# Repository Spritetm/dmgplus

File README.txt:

These are various files for the DMGPlus project. Note that I did this over the time span
of about three years, so there's no plug-and-play recipe to build your own available;
I'd need to reverse my own work to provide that. As such, these files are only provided
as a reference, to plunder if you want to build something similar. For more information
about the DMGPlus project, refer to https://spritesmods.com/?art=dmgplus

The various subdirectories:

* kicad-pcb
This contains the PCB layout. Look at dmgplus-schematic.pdf in that directory if you only want
to look at the schematic without opening Kicad.

* fpga
This contains the Verilog sources for the Ice40 FPGA configuration. You need a proper 
Yosys/nextpnr/icestorm setup to build this.

* linux
This contains the gpio-matrix patch I had to apply to get multiple buttonpresses to work, as
well as the config I use to get the kernel startup to be fast.

* devicetree
The Linux kernel requires a custom device tree to get sound output, DPI RGB on the correct 
pins, and the mapping for the GPIO keyboard matrix; this generates that. Note that you need 
a device tree compiler (e.g. Debian package device-tree-compiler) to build this.

* spi-flash-reader
This compiles and runs under Raspbian. It allows you to read a GameBoy cartridge through the 
Ice40 FPGA via the SPI port. It also allows you to write the reproduction cartridges that are 
around, if you happen to have a similar model to mine.

This directory also contains an initial_init.sh script, which acts as a replacement init
script. It checks the cart inserted and starts up whatever's applicable.

* gnuboy
This is Gnuboy, modified to use the same SPI cart reading method to execute from the actual
cart that is inserted in the DMGPlus unit.

* conv_startupscreen
This is a tool to generate the binary ROM images that can be flashed into a cartridge to 
create a DMGPlus cart. The tool takes a png image that is used as a startup screen, a 
delay, and a game name. The FPGA will display the startup screen for the indicated delay,
the Raspberry Pi can use the game name to start up whatever is required.

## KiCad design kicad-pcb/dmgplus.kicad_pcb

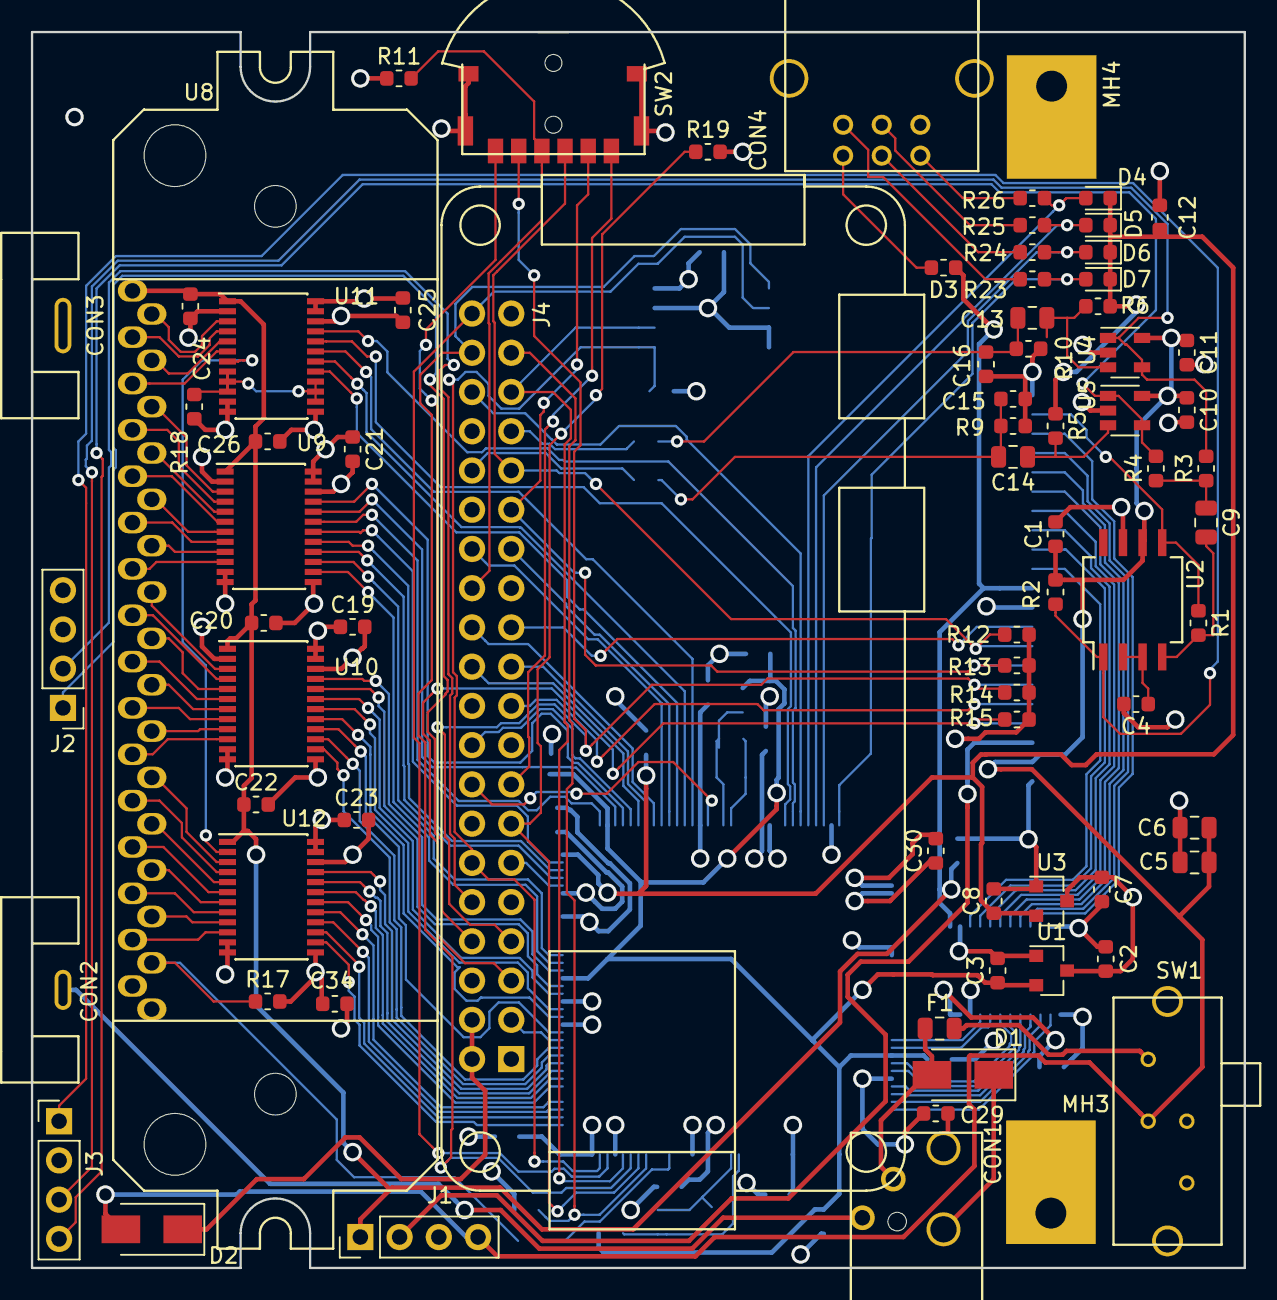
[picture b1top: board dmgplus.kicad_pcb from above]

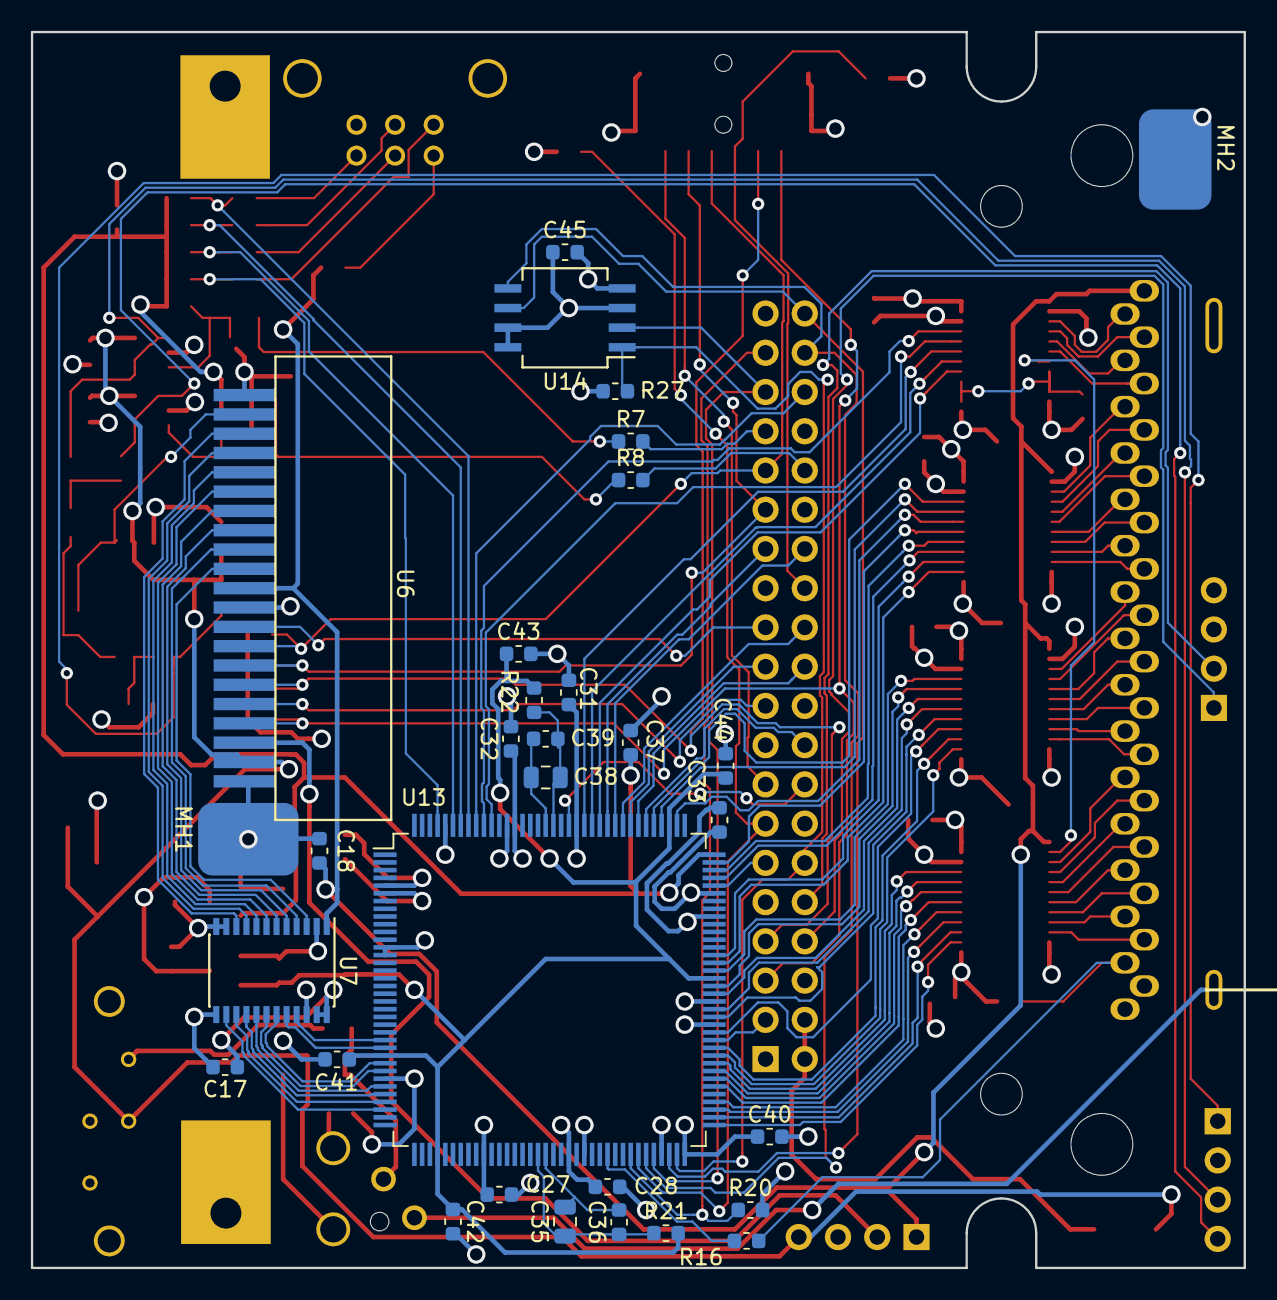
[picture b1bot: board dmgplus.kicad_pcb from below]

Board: 4 copper layers, 78.5 x 80.0 mm, 108 parts (31 on the bottom side), 141 nets.

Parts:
C1, C2, C3, C4, C7, C8: 1uF; C_0603_1608Metric
C5, C6, C9, C13, C14, C35, C38: 10uF; C_0805_2012Metric
C10, C11, C12, C17, C18, C19, C20, C21, C22, C23, C24, C25, C26, C27, C28, C29, C30, C31, C32, C33, C34, C36, C37, C39, C40, C41, C42, C43, C44, C45: 100nF; C_0603_1608Metric
C15, C16: 33nF; C_0603_1608Metric
CON1: BARRELJACK_SW_GB; dmg_pwrjack
CON2: BATCON; dmg_batcon_pos
CON3: BATCON; dmg_batcon_neg
CON4: DMG_LINK_PORT; dmg_linkport
D1: SS16; D_SMA
D2: 1N4001; D_SMA
D3: SS16; R_0603_1608Metric
D4, D5, D6, D7: 1N4148; D_0603_1608Metric
F1: 0.5A; Fuse_0805_2012Metric
J1, J2, J3: Conn_01x04; PinHeader_1x04_P2.54mm_Vertical
J4: Raspberry_Pi_Zero; Raspberry Pi Zero
MH1, MH2: MountingHole_Pad; dmg_grounding_square
MH3, MH4: MountingHole_Pad; dmg_groundhole_square
R1, R2, R11, R12, R13, R14, R15, R17, R18, R19, R20, R27: 10K; R_0603_1608Metric
R3, R4: 20K; R_0603_1608Metric
R5, R6, R16: 4K7; R_0603_1608Metric
R7, R8: 270; R_0603_1608Metric
R9, R10: 150; R_0603_1608Metric
R21, R22: 100; R_0603_1608Metric
R23, R24, R25, R26: 220; R_0603_1608Metric
SW1: SW_DPST; dmg_powersw
SW2: SLLB120x00; Alps_SLLB120x00
U1: XC6206P122; SOT-23
U2: NS8002; SO-8_5.3x6.2mm_P1.27mm
U3: XC6206P252; SOT-23
U4, U5: MCP6021; SOT-23-5
U6: GB_LCD_FLAT; fpc_conn_21pin
U7, U9, U10, U11, U12: 74LVC4245; TSSOP-24_4.4x7.8mm_P0.65mm
U8: GB_PAK; GB_CART_CONN
U13: iCE40-HX4K-TQ144; TQFP-144_20x20mm_P0.5mm
U14: 25LCxxx; SO-8_5.3x6.2mm_P1.27mm

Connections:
1.2V: C3.1, C41.1, C42.1, C43.1, C44.1, R21.2, R22.2, U1.2, U13.27, U13.40, U13.92, U13.111
2.5V: C8.1, C12.1, C37.1, D4.1, D5.1, D6.1, D7.1, R5.1, R6.1, U3.2, U13.108
5VREG: C18.1, C20.1, C22.1, C24.1, C26.1, D3.1, J1.1, U6.11, U7.1, U8.1, U9.1, U10.1, U11.1, U12.1
/Cartridge connector/A0: U8.6, U9.3
/Cartridge connector/A1: U8.7, U9.4
/Cartridge connector/A2: U8.8, U9.5
/Cartridge connector/A3: U8.9, U9.6
/Cartridge connector/A4: U8.10, U9.7
/Cartridge connector/A5: U8.11, U9.8
/Cartridge connector/A6: U8.12, U9.9
/Cartridge connector/A7: U8.13, U9.10
/Cartridge connector/A8: U8.14, U10.3
/Cartridge connector/A9: U8.15, U10.4
/Cartridge connector/A10: U8.16, U10.5
/Cartridge connector/A11: U8.17, U10.6
/Cartridge connector/A12: U8.18, U10.7
/Cartridge connector/A13: U8.19, U10.8
/Cartridge connector/A14: U8.20, U10.9
/Cartridge connector/A15: U8.21, U10.10
/Cartridge connector/CLK: U8.2, U11.3
/Cartridge connector/D0: U8.22, U12.3
/Cartridge connector/D1: U8.23, U12.4
/Cartridge connector/D2: U8.24, U12.5
/Cartridge connector/D3: U8.25, U12.6
/Cartridge connector/D4: U8.26, U12.7
/Cartridge connector/D5: U8.27, U12.8
/Cartridge connector/D6: U8.28, U12.9
/Cartridge connector/D7: U8.29, U12.10
/Cartridge connector/nCS: U8.5, U11.6
/Cartridge connector/nRD: U8.4, U11.5
/Cartridge connector/nWR: U8.3, U11.4
/Power/VBARREL: CON1.2, D1.1
/Power/VBAT_CON: CON1.4, CON2.1
/Power/VBAT_FUSED: F1.2, SW1.1
/Power/VBAT_SW: CON1.3, D1.2, F1.1
BUT_COL1: J4.19, U6.5
BUT_COL2: J4.23, U6.9
BUT_COL3: J4.15, SW2.C
BUT_ROW1: J4.5, R15.2, SW2.1, U6.4
BUT_ROW2: J4.7, R14.2, SW2.2, U6.6
BUT_ROW3: J4.29, R13.2, SW2.4, U6.7
BUT_ROW4: J4.31, R12.2, SW2.3, U6.8
BUT_ROW5: J4.26, R11.2, SW2.T
CART_A0: U9.21, U13.113
CART_A1: U9.20, U13.112
CART_A2: U9.19, U13.110
CART_A3: U9.18, U13.107
CART_A4: U9.17, U13.106
CART_A5: U9.16, U13.105
CART_A6: U9.15, U13.95
CART_A7: U9.14, U13.94
CART_A8: U10.21, U13.93
CART_A9: U10.20, U13.91
CART_A10: U10.19, U13.90
CART_A11: U10.18, U13.88
CART_A12: U10.17, U13.87
CART_A13: U10.16, U13.85
CART_A14: U10.15, U13.83
CART_A15: U10.14, U13.82
CART_BUSDIR: U11.17, U13.120
CART_CLK: U11.21, U13.135
CART_D0: U12.21, U13.81
CART_D1: U12.20, U13.80
CART_D2: U12.19, U13.79
CART_D3: U12.18, U13.78
CART_D4: U12.17, U13.76
CART_D5: U12.16, U13.75
CART_D6: U12.15, U13.74
CART_D7: U12.14, U13.73
CART_NRST: R16.2, U13.62
CART_nCS: U11.18, U13.121
CART_nRD: U11.19, U13.122
CART_nWR: U11.20, U13.134
FLASH_MISO: J4.35, U13.68, U14.2
FLASH_MOSI: J4.38, U13.67, U14.5
FLASH_SCK: J4.40, U13.70, U14.6
FLASH_nCS: J4.12, R27.2, U13.71, U14.1
FPGA_DONE: J4.37, R20.1, U13.65
FPGA_nRESET: J4.13, R19.1, U13.66
GND: C1.2, C2.2, C3.2, C4.2, C5.2, C6.2, C7.2, C8.2, C10.2, C11.2, C12.2, C15.2, C16.2, C17.2, C18.2, C19.2, C20.2, C21.2, C22.2, C23.2, C24.2, C25.2, C26.2, C27.2, C28.2, C29.2, C30.2, C31.2, C32.2, C33.2, C34.2, C37.2, C40.2, C41.2, C42.2, C43.2, C44.2, C45.2, CON1.1, CON3.1, CON4.6, CON4.7, CON4.8, J1.3, J2.4, J3.2, J4.6, J4.9, J4.14, J4.20, J4.25, J4.30, J4.34, J4.39, MH1.1, MH2.1, MH3.1, MH4.1, R9.2, R10.2, R17.2, R18.2, SW2.M1, SW2.M2, SW2.M3, SW2.M4, U1.1, U2.7, U3.1, U4.2, U5.2, U6.1, U6.10, U6.21, U7.2, U7.11, U7.12, U7.13, U7.22, U8.32, U9.2, U9.11, U9.12, U9.13, U9.22, U10.2, U10.11, U10.12, U10.13, U10.22, U11.2, U11.11, U11.12, U11.13, U11.22, U12.11, U12.12, U12.13, U12.22, U13.5, U13.13, U13.14, U13.59, U13.69, U13.86, U13.103, U13.132, U13.140, U14.4
LCDALTSIG: U7.20, U13.26
LCDCLK: U7.19, U13.28
LCDCONTROL: U7.14, U13.34
LCDD0: U7.17, U13.31
LCDD1: U7.18, U13.29
LCDDATAL: U7.15, U13.33
LCDHSYNC: U7.16, U13.32
LCDVSYNC: U7.21, U13.25
LP_CLK: D4.2, R26.2, U13.137
LP_DIN: D6.2, R24.2, U13.139
LP_DOUT: D7.2, R23.2, U13.141
LP_GP: D5.2, R25.2, U13.138
unnamed: C4.1, U2.2, U2.3
unnamed: C9.1, R3.1, R4.1
unnamed: C9.2, R1.2, U2.4
unnamed: C13.1, C16.1, R7.1, R10.1
unnamed: C13.2, R6.2, U4.3
unnamed: C14.1, R5.2, U5.3
unnamed: C14.2, C15.1, R8.1, R9.1
unnamed: C35.1, C36.1, R21.1, U13.53
unnamed: C35.2, C36.2, U13.54
unnamed: C38.1, C39.1, R22.1, U13.126
unnamed: C38.2, C39.2, U13.127
unnamed: CON4.1, D3.2
unnamed: CON4.2, R23.1
unnamed: CON4.3, R24.1
unnamed: CON4.4, R25.1
unnamed: CON4.5, R26.1
unnamed: J2.1, J4.8
unnamed: J2.2, J4.10
unnamed: J3.1, R2.2, U2.1
unnamed: J3.3, R3.2, U4.1, U4.4
unnamed: J3.4, R4.2, U5.1, U5.4
unnamed: J4.32, R8.2
unnamed: J4.33, R7.2
unnamed: R16.1, R17.1, U8.30
unnamed: R18.1, U11.8, U11.9, U11.10, U11.14, U11.15, U11.16
unnamed: U6.12, U7.3
unnamed: U6.13, U7.4
unnamed: U6.14, U7.5
unnamed: U6.15, U7.6
unnamed: U6.16, U7.7
unnamed: U6.17, U7.8
unnamed: U6.18, U7.9
unnamed: U6.19, U7.10
unnamed: U11.7, U12.2
RPI_B0: J4.24, U13.117
RPI_B1: J4.21, U13.116
RPI_DATAEN: J4.28, U13.118
RPI_G0: J4.16, U13.124
RPI_G1: J4.18, U13.114
RPI_G2: J4.22, U13.115
RPI_PCLK: J4.27, U13.119
RPI_PWR: D2.1, J4.2, J4.4
RPI_R0: J4.36, U13.136
RPI_R1: J4.11, U13.104
RPI_VSYNC: J4.3, U13.84
SPK: R1.1, U2.5, U6.20
VBAT: C1.1, C5.1, C6.1, C10.1, C11.1, D2.2, J1.4, R2.1, SW1.2, U2.6, U4.5, U5.5, U6.2
VCC: C2.1, C7.1, C17.1, C19.1, C21.1, C23.1, C25.1, C27.1, C28.1, C29.1, C30.1, C31.1, C32.1, C33.1, C34.1, C40.1, C45.1, J4.1, J4.17, R11.1, R12.1, R13.1, R14.1, R15.1, R19.2, R20.2, R27.1, U1.3, U3.3, U7.23, U7.24, U9.23, U9.24, U10.23, U10.24, U11.23, U11.24, U12.23, U12.24, U13.6, U13.30, U13.46, U13.57, U13.72, U13.89, U13.100, U13.123, U13.131, U14.3, U14.7, U14.8
VLCDNEG: J1.2, U6.3

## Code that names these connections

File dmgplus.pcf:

# Physical Constraints File for dmgplus.
# dmgplus has a ICe40HX4K-TQ144 chip.

set_io lcd_vsync 25
set_io lcd_altsig 26
set_io lcd_clk 28
set_io lcd_d[1] 29
set_io lcd_d[0] 31
set_io lcd_hsync 32
set_io lcd_datal 33
set_io lcd_control 34
set_io cart_a[2] 110
set_io cart_a[1] 112
set_io cart_a[0] 113
set_io rpi_g[1] 114
set_io rpi_g[2] 115
set_io rpi_b[1] 116
set_io rpi_b[0] 117
set_io rpi_dataen 118
set_io rpi_pclk 119
set_io cart_busdir 120
set_io cart_ncs 121
set_io cart_nrd 122
set_io rpi_g[0] 124
set_io cart_nwr 134
set_io cart_clk 135
set_io rpi_r[0] 136
set_io lp_clk 137
set_io lp_gp 138
set_io lp_din 139
set_io lp_dout 141
set_io cart_d[7] 73
set_io cart_d[6] 74
set_io cart_d[5] 75
set_io cart_d[4] 76
set_io cart_d[3] 78
set_io cart_d[2] 79
set_io cart_d[1] 80
set_io cart_d[0] 81
set_io cart_a[15] 82
set_io cart_a[14] 83
set_io rpi_vsync 84
set_io cart_a[13] 85
set_io cart_a[12] 87
set_io cart_a[11] 88
set_io cart_a[10] 90
set_io cart_a[9] 91
set_io cart_a[8] 93
set_io cart_a[7] 94
set_io cart_a[6] 95
set_io rpi_r[1] 104
set_io cart_a[5] 105
set_io cart_a[4] 106
set_io cart_a[3] 107
set_io cart_nrst 62
set_io spi_mosi 67
set_io spi_miso 68
set_io spi_sck 70
set_io spi_cs 71
set_io pwm_l 101
set_io pwm_r 102

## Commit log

2018-08-04 First commit. Can show test pattern on dmg screen.
2018-08-05 Add code to sample video port of rpi
2018-08-05 Shit works! Q3A on a DMG screen is too funny.
2018-08-19 Nice interleaving and stuff
2018-08-24 Port to Ice40
2018-08-26 Got startup screen, yay!
2018-08-26 Nintendo logo scrolling down works at right speed now
2018-08-29 Add pli-DING! startup sound generation logic; fix dithering logic to properly show grays
2018-08-30 Fix busy gen interpretation
2019-01-13 Add attempt at spi slave interface, plus testbed for it
2019-01-13 Spi slave seems to work under normal conditions.
2019-01-24 Create prelim spicart (spi<->cart iface) + testbench
2019-01-26 Simulates, synthesis has a snafu
2019-01-27 Simu works... why does synth not do the thing it should do?
2019-01-27 Spislave now also works in synth.
2019-01-27 Read >4 bytes ok
2019-01-28 Reading 0-16K seems to work.
2019-02-06 Change from C90 to C99 standard. I like my one-line comments.
2019-03-16 Error: fails at 0xAAB
2019-03-17 Startup logo and SPI works.
2019-03-17 Splash screen support.
2019-03-18 Dmgplus splash and delay works
2019-03-18 Do not break rpi initial cart reading in lieu of fancy splash screen
2019-03-18 Faffing around with making programming work
2021-06-11 Modify FPGA flow: arachne -> nextpnr
2021-06-11 Cleanup files for old toolchains/silicon
2021-06-11 Do proper clock domain crossing of rpi rgb to vram, this removes artifacts on the screen. Also tweak ring osc stages; nextpnr made it too fast ^_^
2021-06-20 Small fixes
2021-06-26 Tweak logo / splashscreen timings
2021-06-27 Add devicetree stuff
2021-06-27 Improve dithering
2021-06-27 Move fpga things into its own subdir
2021-06-27 Add vram
2021-06-27 Add KiCad PCB design files
2021-06-27 add hexdump files
2021-06-27 Add initial init and gitignore files
2021-06-27 Autoconfig changes
2021-06-27 dmgplus interfacing
2021-06-27 move gnuboy repo into directory
2021-06-27 Move spi-flash-reader stuff into its own subdir
2021-06-27 Linux kernel stuff
2021-06-27 Licensing, add README
